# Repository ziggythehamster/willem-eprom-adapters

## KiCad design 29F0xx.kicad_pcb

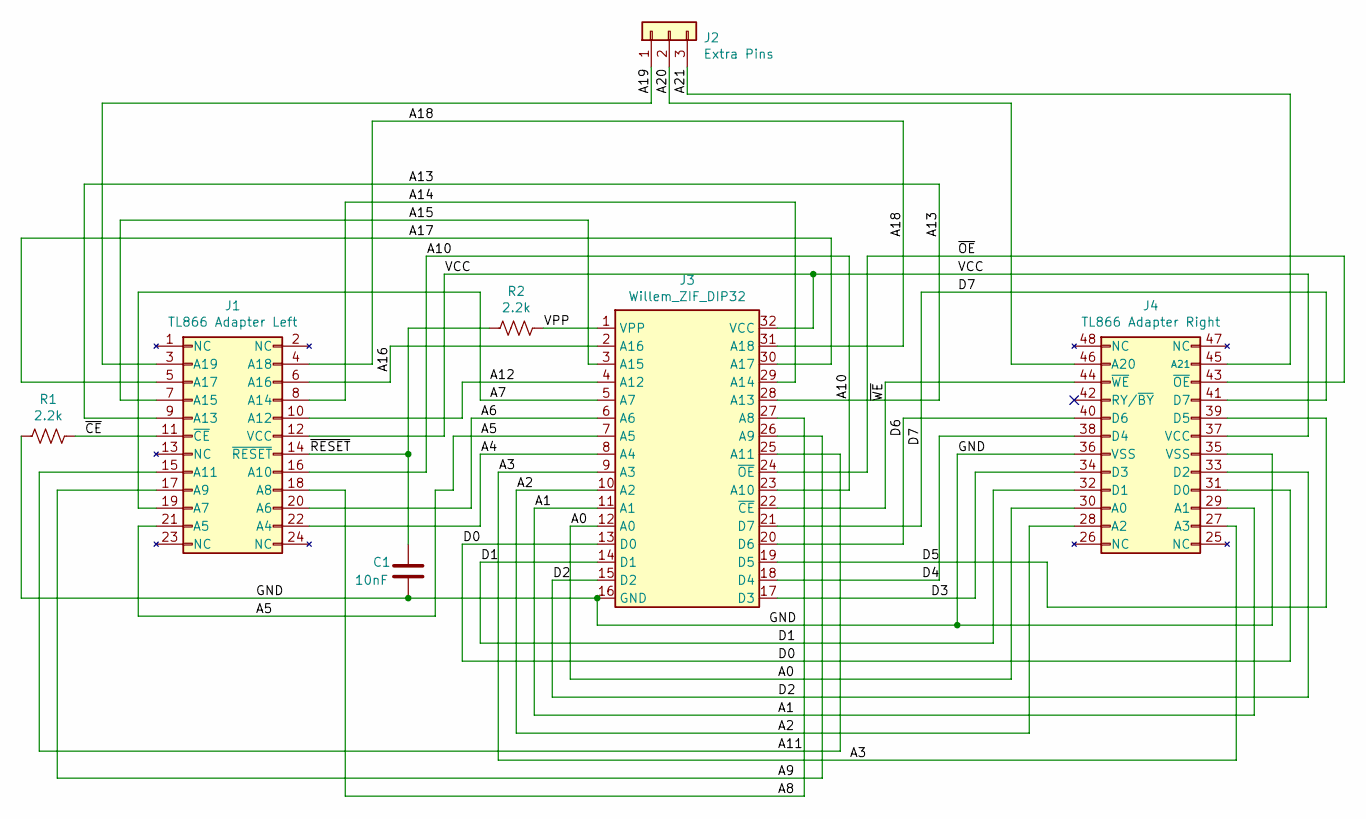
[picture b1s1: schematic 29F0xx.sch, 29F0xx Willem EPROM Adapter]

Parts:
C1: 10nF; C_Disc_D3.8mm_W2.6mm_P2.50mm
J1: TL866 Adapter Left; PinHeader_2x12_P2.54mm_Vertical
J2: Extra Pins; PinHeader_1x03_P2.54mm_Vertical
J3: Willem_ZIF_DIP32; DIP-32_W15.24mm_Socket_LongPads
J4: TL866 Adapter Right; PinHeader_2x12_P2.54mm_Vertical_25-48
R1, R2: 2.2k; R_Axial_DIN0309_L9.0mm_D3.2mm_P15.24mm_Horizontal

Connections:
/A0: J3.12 (A0), J4.30 (A0)
/A1: J3.11 (A1), J4.29 (A1)
/A2: J3.10 (A2), J4.28 (A2)
/A3: J3.9 (A3), J4.27 (A3)
/A4: J1.22 (A4), J3.8 (A4)
/A5: J1.21 (A5), J3.7 (A5)
/A6: J1.20 (A6), J3.6 (A6)
/A7: J1.19 (A7), J3.5 (A7)
/A8: J1.18 (A8), J3.27 (A8)
/A9: J1.17 (A9), J3.26 (A9)
/A10: J1.16 (A10), J3.23 (A10)
/A11: J1.15 (A11), J3.25 (A11)
/A12: J1.10 (A12), J3.4 (A12)
/A13: J1.9 (A13), J3.28 (A13)
/A14: J1.8 (A14), J3.29 (A14)
/A15: J1.7 (A15), J3.3 (A15)
/A16: J1.6 (A16), J3.2 (A16)
/A17: J1.5 (A17), J3.30 (A17)
/A18: J1.4 (A18), J3.31 (A18)
/A19: J1.3 (A19), J2.1
/A20: J2.2, J4.46 (A20)
/A21: J2.3, J4.45 (A21)
/D0: J3.13 (D0), J4.31 (D0)
/D1: J3.14 (D1), J4.32 (D1)
/D2: J3.15 (D2), J4.33 (D2)
/D3: J3.17 (D3), J4.34 (D3)
/D4: J3.18 (D4), J4.38 (D4)
/D5: J3.19 (D5), J4.39 (D5)
/D6: J3.20 (D6), J4.40 (D6)
/D7: J3.21 (D7), J4.41 (D7)
/GND: C1.2, J3.16 (GND), J4.35 (VSS), J4.36 (VSS), R1.2
/VCC: J1.12 (VCC), J3.32 (VCC), J4.37 (VCC)
/VPP: J3.1 (VPP), R2.1
/~CE: J1.11 (~CE), R1.1
/~OE: J3.24 (~OE), J4.43 (~OE)
/~RESET: C1.1, J1.14 (~RESET), R2.2
/~WE: J3.22 (~CE), J4.44 (~WE)

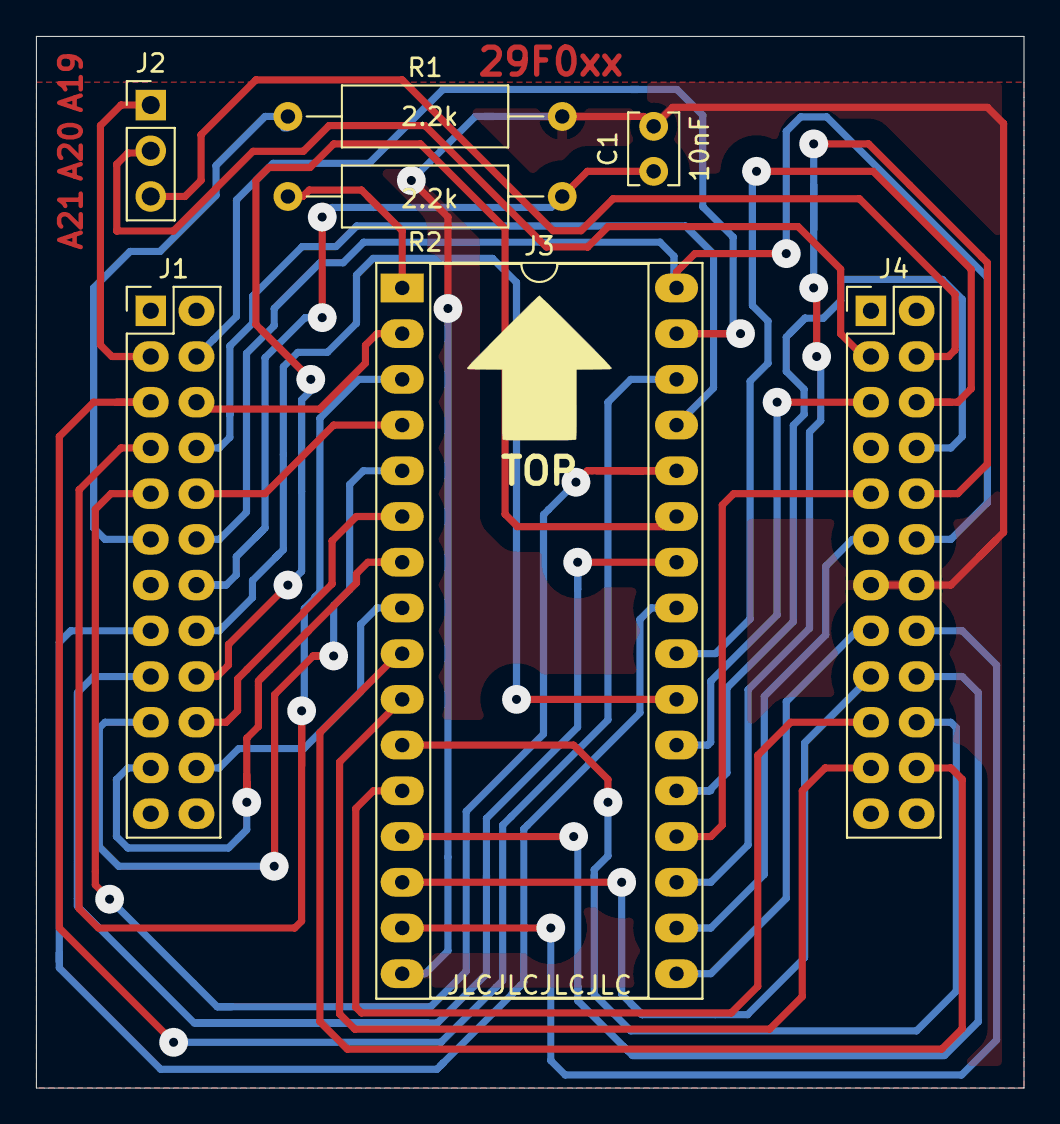
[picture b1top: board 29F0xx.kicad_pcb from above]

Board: 2 copper layers, 54.9 x 58.4 mm, 7 parts (0 on the bottom side), 37 nets.

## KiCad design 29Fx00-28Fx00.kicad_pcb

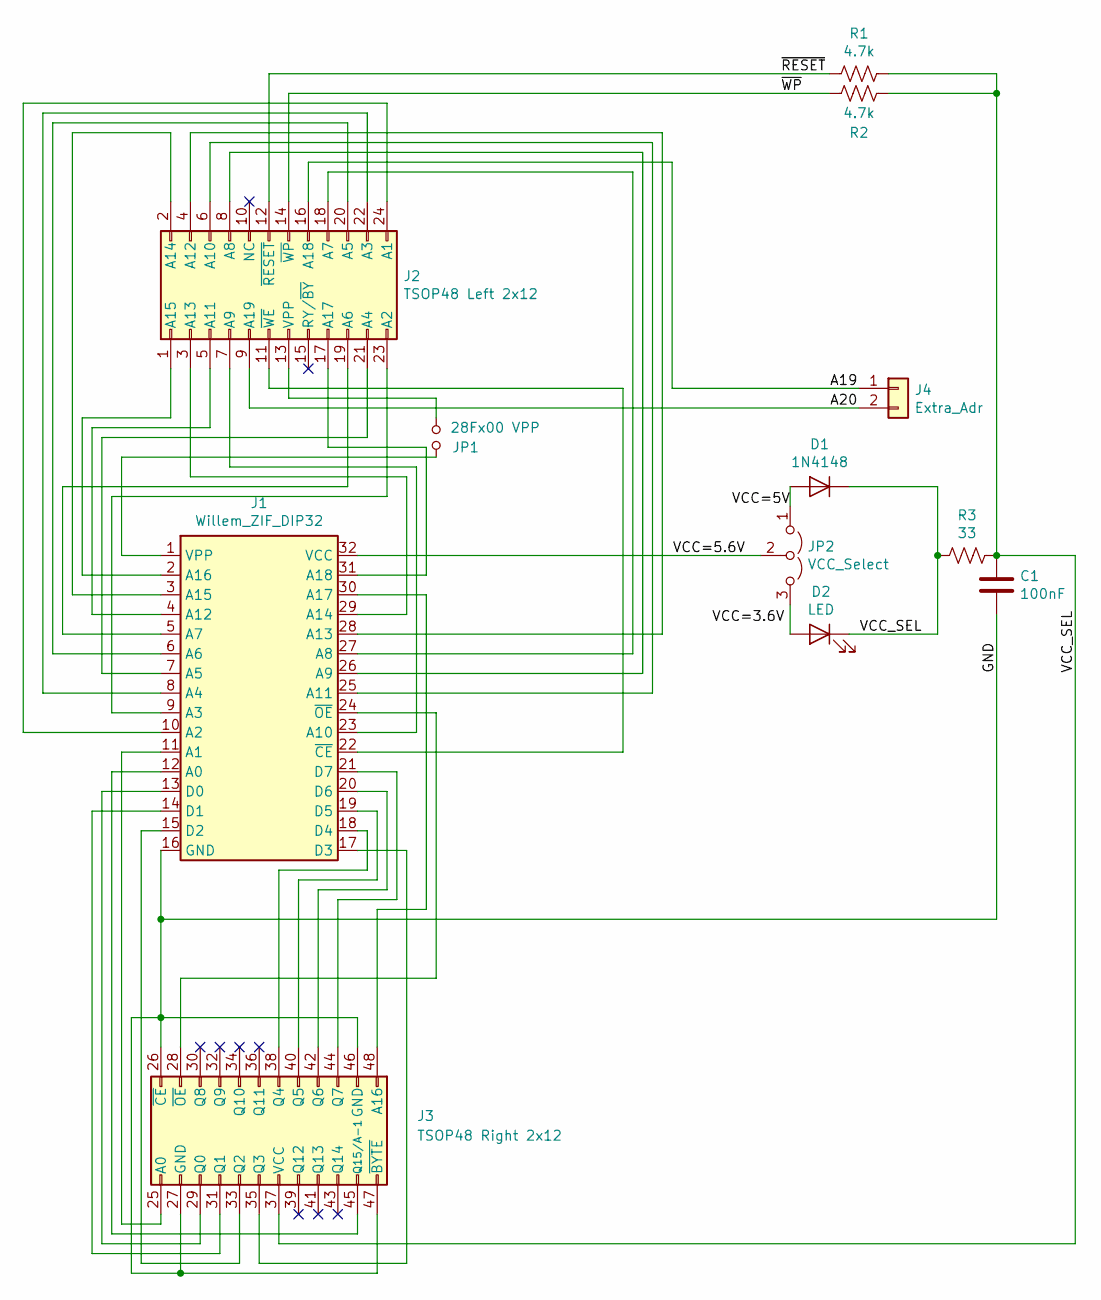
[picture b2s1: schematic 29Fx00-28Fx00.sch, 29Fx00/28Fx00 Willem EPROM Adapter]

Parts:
C1: 100nF; C_Disc_D3.8mm_W2.6mm_P2.50mm
D1: 1N4148; D_DO-35_SOD27_P7.62mm_Horizontal
D2: LED; LED_D3.0mm
J1: Willem_ZIF_DIP32; DIP-32_W15.24mm_Socket_LongPads
J2: TSOP48 Left 2x12; PinHeader_2x12_P2.54mm_Vertical
J3: TSOP48 Right 2x12; PinHeader_2x12_P2.54mm_Vertical_25-48
J4: Extra_Adr; PinHeader_1x02_P2.54mm_Vertical
JP1: 28Fx00 VPP; PinHeader_1x02_P2.54mm_Vertical
JP2: VCC_Select; PinHeader_1x03_P2.54mm_Vertical
R1, R2: 4.7k; R_Axial_DIN0309_L9.0mm_D3.2mm_P15.24mm_Horizontal
R3: 33; R_Axial_DIN0309_L9.0mm_D3.2mm_P15.24mm_Horizontal

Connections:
/A19: J2.16 (A18), J4.1
/A20: J2.9 (A19), J4.2
/GND: C1.2, J1.16 (GND), J3.26 (~CE), J3.27 (GND), J3.46 (GND), J3.47 (~BYTE)
/VCC=5.6V: J1.32 (VCC), JP2.2 (C)
/~RESET: J2.12 (~RESET), R1.2
/~WP: J2.14 (~WP), R2.2
unnamed: D1.2 (A), JP2.1 (A)
unnamed: D2.2 (A), JP2.3 (B)
unnamed: J1.1 (VPP), JP1.1
unnamed: J1.2 (A16), J2.1 (A15)
unnamed: J1.3 (A15), J2.2 (A14)
unnamed: J1.4 (A12), J2.5 (A11)
unnamed: J1.5 (A7), J2.19 (A6)
unnamed: J1.6 (A6), J2.20 (A5)
unnamed: J1.7 (A5), J2.21 (A4)
unnamed: J1.8 (A4), J2.22 (A3)
unnamed: J1.9 (A3), J2.23 (A2)
unnamed: J1.10 (A2), J2.24 (A1)
unnamed: J1.11 (A1), J3.25 (A0)
unnamed: J1.12 (A0), J3.45 (Q15/A-1)
unnamed: J1.13 (D0), J3.29 (Q0)
unnamed: J1.14 (D1), J3.31 (Q1)
unnamed: J1.15 (D2), J3.33 (Q2)
unnamed: J1.17 (D3), J3.35 (Q3)
unnamed: J1.18 (D4), J3.38 (Q4)
unnamed: J1.19 (D5), J3.40 (Q5)
unnamed: J1.20 (D6), J3.42 (Q6)
unnamed: J1.21 (D7), J3.44 (Q7)
unnamed: J1.22 (~CE), J2.11 (~WE)
unnamed: J1.23 (A10), J2.7 (A9)
unnamed: J1.24 (~OE), J3.28 (~OE)
unnamed: J1.25 (A11), J2.6 (A10)
unnamed: J1.26 (A9), J2.8 (A8)
unnamed: J1.27 (A8), J2.18 (A7)
unnamed: J1.28 (A13), J2.4 (A12)
unnamed: J1.29 (A14), J2.3 (A13)
unnamed: J1.30 (A17), J3.48 (A16)
unnamed: J1.31 (A18), J2.17 (A17)
unnamed: J2.13 (VPP), JP1.2

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
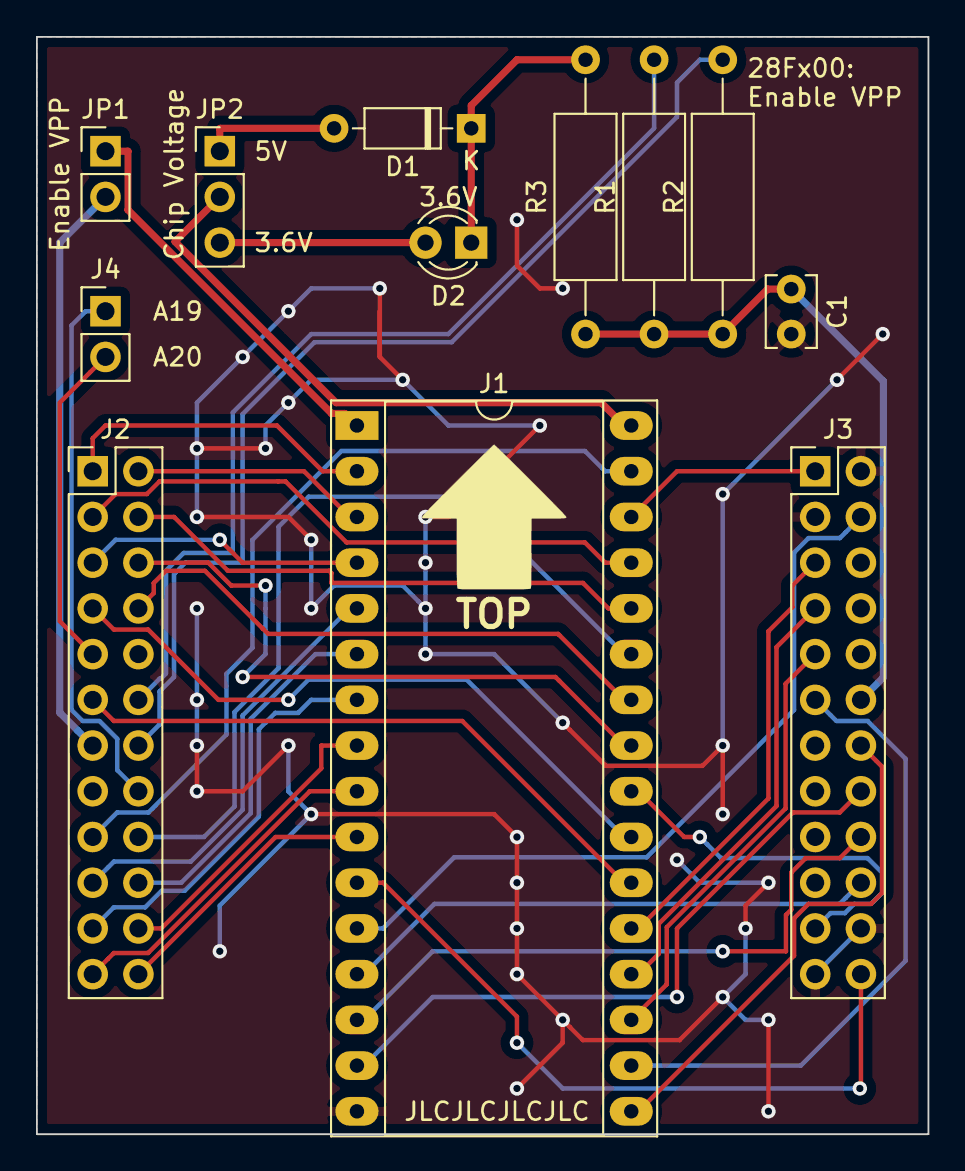
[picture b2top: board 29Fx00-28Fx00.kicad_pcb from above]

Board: 2 copper layers, 49.5 x 61.0 mm, 12 parts (0 on the bottom side), 41 nets.

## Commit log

2020-12-29 Root commit
2020-12-29 Add 29Fx00/28Fx00 adapter
2021-01-02 Add parts for the 29F0xx
2021-01-02 Add 29F0xx initial version
2021-01-02 Add schematic for 29Fx00/28Fx00
2021-01-11 Make the pads bigger
2021-01-11 Change page size, update footprints
2021-01-11 Redo with looser tolerances
2021-01-11 Updated project file
